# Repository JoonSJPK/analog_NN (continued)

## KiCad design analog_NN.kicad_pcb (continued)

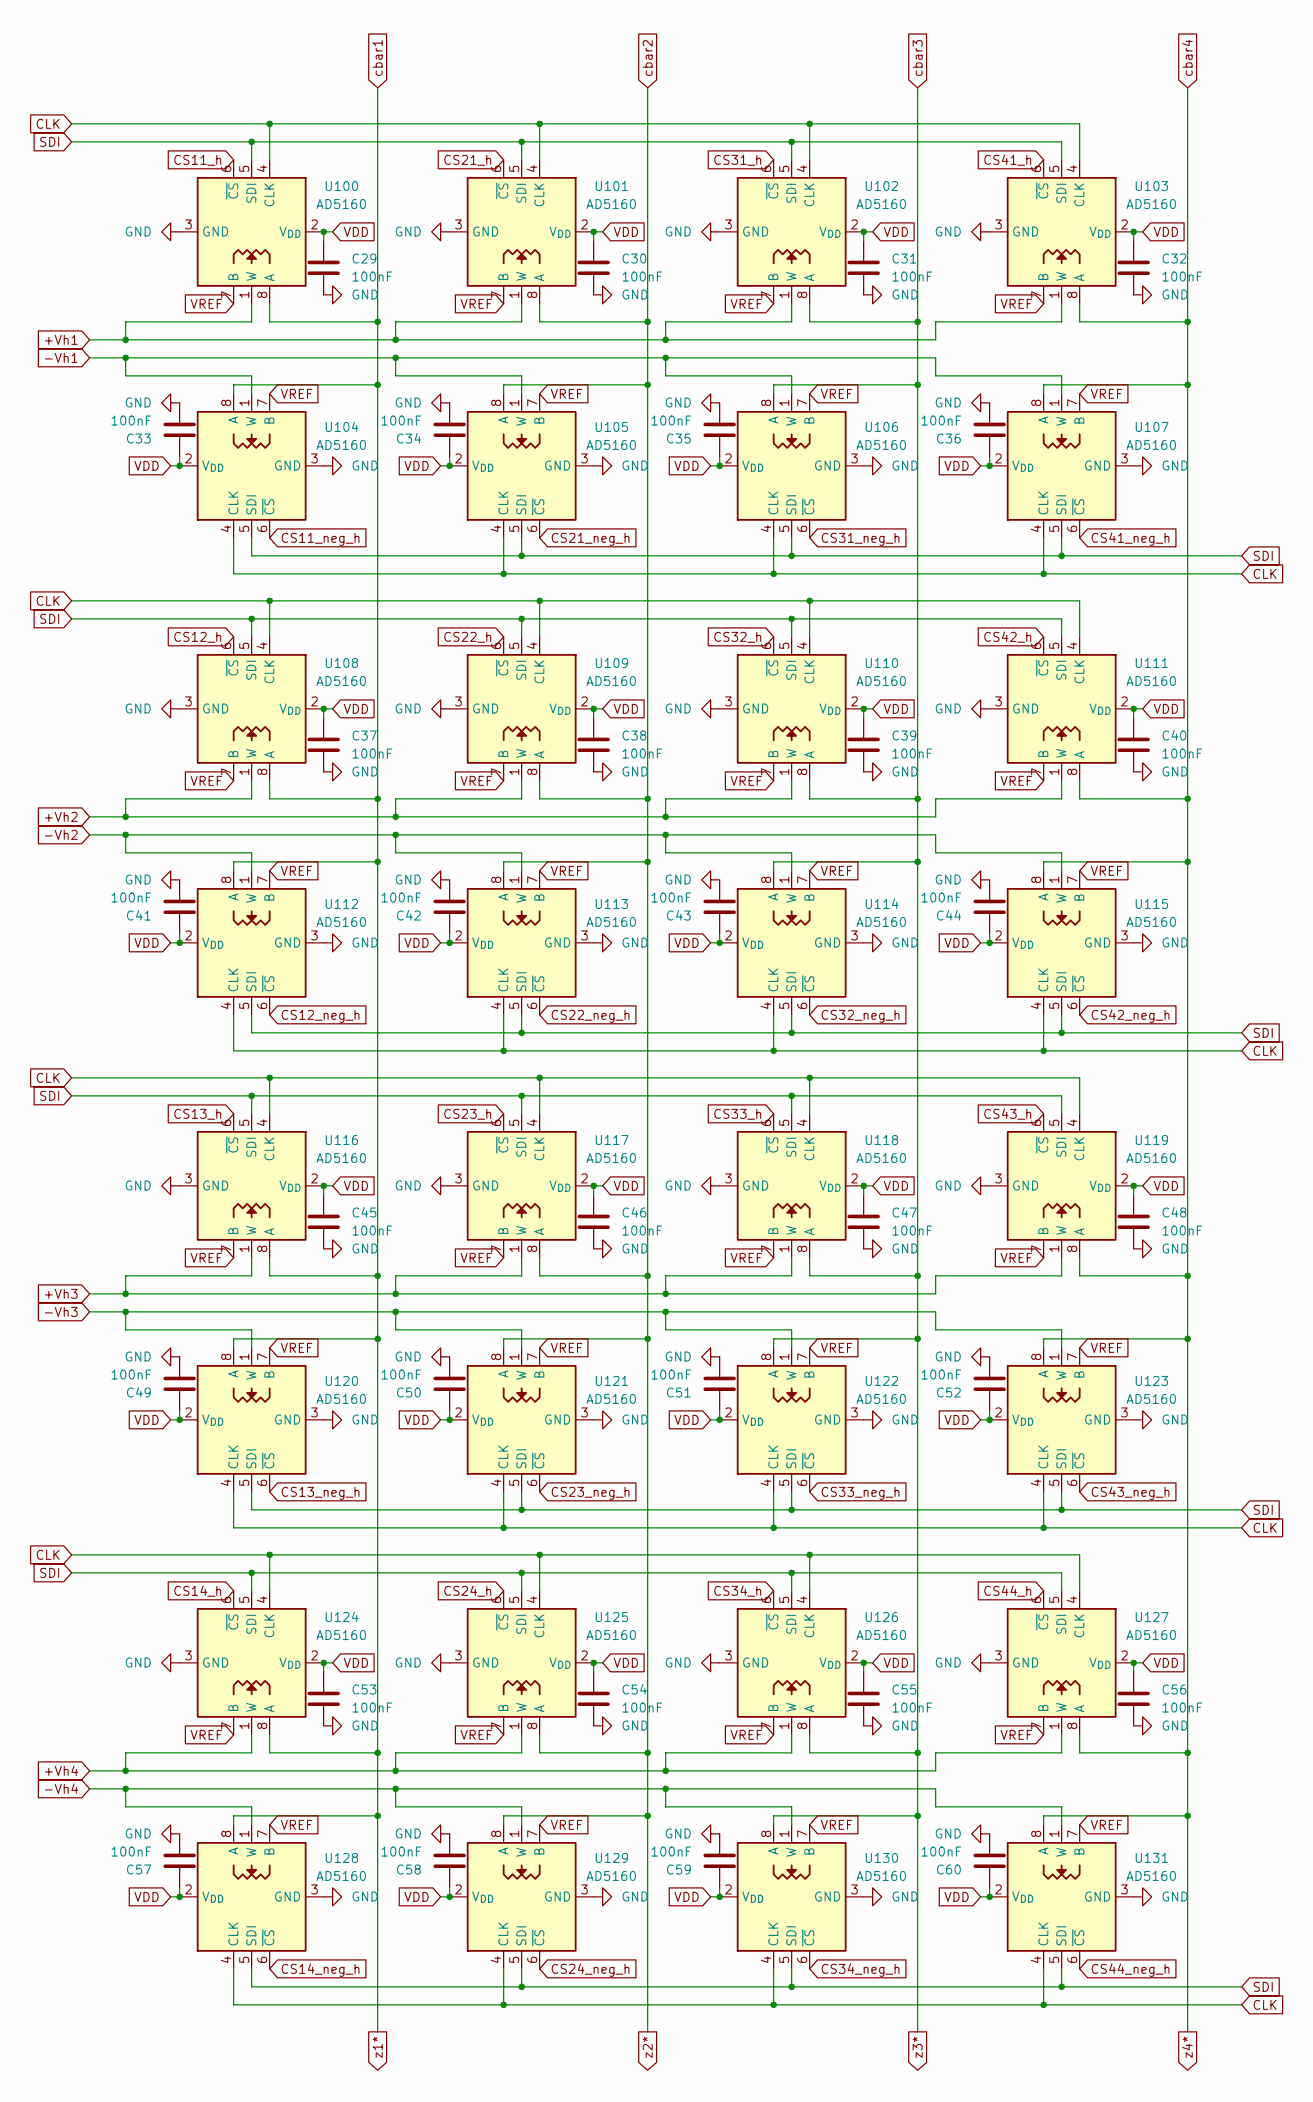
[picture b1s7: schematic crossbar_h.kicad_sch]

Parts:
C29, C30, C31, C32, C33, C34, C35, C36, C37, C38, C39, C40, C41, C42, C43, C44, C45, C46, C47, C48, C49, C50, C51, C52, C53, C54, C55, C56, C57, C58, C59, C60: 100nF; C_1206_3216Metric
U100, U101, U102, U103, U104, U105, U106, U107, U108, U109, U110, U111, U112, U113, U114, U115, U116, U117, U118, U119, U120, U121, U122, U123, U124, U125, U126, U127, U128, U129, U130, U131: AD5160; SOT-23-8

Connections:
+Vh1: U100.1 (W), U101.1 (W), U102.1 (W), U103.1 (W)
+Vh2: U108.1 (W), U109.1 (W), U110.1 (W), U111.1 (W)
+Vh3: U116.1 (W), U117.1 (W), U118.1 (W), U119.1 (W)
+Vh4: U124.1 (W), U125.1 (W), U126.1 (W), U127.1 (W)
-Vh1: U104.1 (W), U105.1 (W), U106.1 (W), U107.1 (W); also elsewhere on the board
-Vh2: U112.1 (W), U113.1 (W), U114.1 (W), U115.1 (W); also elsewhere on the board
-Vh3: U120.1 (W), U121.1 (W), U122.1 (W), U123.1 (W); also elsewhere on the board
-Vh4: U128.1 (W), U129.1 (W), U130.1 (W), U131.1 (W); also elsewhere on the board
CLK: U100.4 (CLK), U101.4 (CLK), U102.4 (CLK), U103.4 (CLK), U104.4 (CLK), U105.4 (CLK), U106.4 (CLK), U107.4 (CLK), U108.4 (CLK), U109.4 (CLK), U110.4 (CLK), U111.4 (CLK), U112.4 (CLK), U113.4 (CLK), U114.4 (CLK), U115.4 (CLK), U116.4 (CLK), U117.4 (CLK), U118.4 (CLK), U119.4 (CLK), U120.4 (CLK), U121.4 (CLK), U122.4 (CLK), U123.4 (CLK), U124.4 (CLK), U125.4 (CLK), U126.4 (CLK), U127.4 (CLK), U128.4 (CLK), U129.4 (CLK), U130.4 (CLK), U131.4 (CLK); also elsewhere on the board
CS11_h: U100.6 (~CS); also elsewhere on the board
CS11_neg_h: U104.6 (~CS); also elsewhere on the board
CS12_h: U108.6 (~CS); also elsewhere on the board
CS12_neg_h: U112.6 (~CS); also elsewhere on the board
CS13_h: U116.6 (~CS); also elsewhere on the board
CS13_neg_h: U120.6 (~CS); also elsewhere on the board
CS14_h: U124.6 (~CS); also elsewhere on the board
CS14_neg_h: U128.6 (~CS); also elsewhere on the board
CS21_h: U101.6 (~CS); also elsewhere on the board
CS21_neg_h: U105.6 (~CS); also elsewhere on the board
CS22_h: U109.6 (~CS); also elsewhere on the board
CS22_neg_h: U113.6 (~CS); also elsewhere on the board
CS23_h: U117.6 (~CS); also elsewhere on the board
CS23_neg_h: U121.6 (~CS); also elsewhere on the board
CS24_h: U125.6 (~CS); also elsewhere on the board
CS24_neg_h: U129.6 (~CS); also elsewhere on the board
CS31_h: U102.6 (~CS); also elsewhere on the board
CS31_neg_h: U106.6 (~CS); also elsewhere on the board
CS32_h: U110.6 (~CS); also elsewhere on the board
CS32_neg_h: U114.6 (~CS); also elsewhere on the board
CS33_h: U118.6 (~CS); also elsewhere on the board
CS33_neg_h: U122.6 (~CS); also elsewhere on the board
CS34_h: U126.6 (~CS); also elsewhere on the board
CS34_neg_h: U130.6 (~CS); also elsewhere on the board
CS41_h: U103.6 (~CS); also elsewhere on the board
CS41_neg_h: U107.6 (~CS); also elsewhere on the board
CS42_h: U111.6 (~CS); also elsewhere on the board
CS42_neg_h: U115.6 (~CS); also elsewhere on the board
CS43_h: U119.6 (~CS); also elsewhere on the board
CS43_neg_h: U123.6 (~CS); also elsewhere on the board
CS44_h: U127.6 (~CS); also elsewhere on the board
CS44_neg_h: U131.6 (~CS); also elsewhere on the board
GND: C29.2, C30.2, C31.2, C32.2, C33.2, C34.2, C35.2, C36.2, C37.2, C38.2, C39.2, C40.2, C41.2, C42.2, C43.2, C44.2, C45.2, C46.2, C47.2, C48.2, C49.2, C50.2, C51.2, C52.2, C53.2, C54.2, C55.2, C56.2, C57.2, C58.2, C59.2, C60.2, U100.3 (GND), U101.3 (GND), U102.3 (GND), U103.3 (GND), U104.3 (GND), U105.3 (GND), U106.3 (GND), U107.3 (GND), U108.3 (GND), U109.3 (GND), U110.3 (GND), U111.3 (GND), U112.3 (GND), U113.3 (GND), U114.3 (GND), U115.3 (GND), U116.3 (GND), U117.3 (GND), U118.3 (GND), U119.3 (GND), U120.3 (GND), U121.3 (GND), U122.3 (GND), U123.3 (GND), U124.3 (GND), U125.3 (GND), U126.3 (GND), U127.3 (GND), U128.3 (GND), U129.3 (GND), U130.3 (GND), U131.3 (GND); also elsewhere on the board
SDI: U100.5 (SDI), U101.5 (SDI), U102.5 (SDI), U103.5 (SDI), U104.5 (SDI), U105.5 (SDI), U106.5 (SDI), U107.5 (SDI), U108.5 (SDI), U109.5 (SDI), U110.5 (SDI), U111.5 (SDI), U112.5 (SDI), U113.5 (SDI), U114.5 (SDI), U115.5 (SDI), U116.5 (SDI), U117.5 (SDI), U118.5 (SDI), U119.5 (SDI), U120.5 (SDI), U121.5 (SDI), U122.5 (SDI), U123.5 (SDI), U124.5 (SDI), U125.5 (SDI), U126.5 (SDI), U127.5 (SDI), U128.5 (SDI), U129.5 (SDI), U130.5 (SDI), U131.5 (SDI); also elsewhere on the board
VDD: C29.1, C30.1, C31.1, C32.1, C33.1, C34.1, C35.1, C36.1, C37.1, C38.1, C39.1, C40.1, C41.1, C42.1, C43.1, C44.1, C45.1, C46.1, C47.1, C48.1, C49.1, C50.1, C51.1, C52.1, C53.1, C54.1, C55.1, C56.1, C57.1, C58.1, C59.1, C60.1, U100.2 (V_{DD}), U101.2 (V_{DD}), U102.2 (V_{DD}), U103.2 (V_{DD}), U104.2 (V_{DD}), U105.2 (V_{DD}), U106.2 (V_{DD}), U107.2 (V_{DD}), U108.2 (V_{DD}), U109.2 (V_{DD}), U110.2 (V_{DD}), U111.2 (V_{DD}), U112.2 (V_{DD}), U113.2 (V_{DD}), U114.2 (V_{DD}), U115.2 (V_{DD}), U116.2 (V_{DD}), U117.2 (V_{DD}), U118.2 (V_{DD}), U119.2 (V_{DD}), U120.2 (V_{DD}), U121.2 (V_{DD}), U122.2 (V_{DD}), U123.2 (V_{DD}), U124.2 (V_{DD}), U125.2 (V_{DD}), U126.2 (V_{DD}), U127.2 (V_{DD}), U128.2 (V_{DD}), U129.2 (V_{DD}), U130.2 (V_{DD}), U131.2 (V_{DD}); also elsewhere on the board
VREF: U100.7 (B), U101.7 (B), U102.7 (B), U103.7 (B), U104.7 (B), U105.7 (B), U106.7 (B), U107.7 (B), U108.7 (B), U109.7 (B), U110.7 (B), U111.7 (B), U112.7 (B), U113.7 (B), U114.7 (B), U115.7 (B), U116.7 (B), U117.7 (B), U118.7 (B), U119.7 (B), U120.7 (B), U121.7 (B), U122.7 (B), U123.7 (B), U124.7 (B), U125.7 (B), U126.7 (B), U127.7 (B), U128.7 (B), U129.7 (B), U130.7 (B), U131.7 (B); also elsewhere on the board
cbar1: U100.8 (A), U104.8 (A), U108.8 (A), U112.8 (A), U116.8 (A), U120.8 (A), U124.8 (A), U128.8 (A); also elsewhere on the board
cbar2: U101.8 (A), U105.8 (A), U109.8 (A), U113.8 (A), U117.8 (A), U121.8 (A), U125.8 (A), U129.8 (A); also elsewhere on the board
cbar3: U102.8 (A), U106.8 (A), U110.8 (A), U114.8 (A), U118.8 (A), U122.8 (A), U126.8 (A), U130.8 (A); also elsewhere on the board
cbar4: U103.8 (A), U107.8 (A), U111.8 (A), U115.8 (A), U119.8 (A), U123.8 (A), U127.8 (A), U131.8 (A); also elsewhere on the board

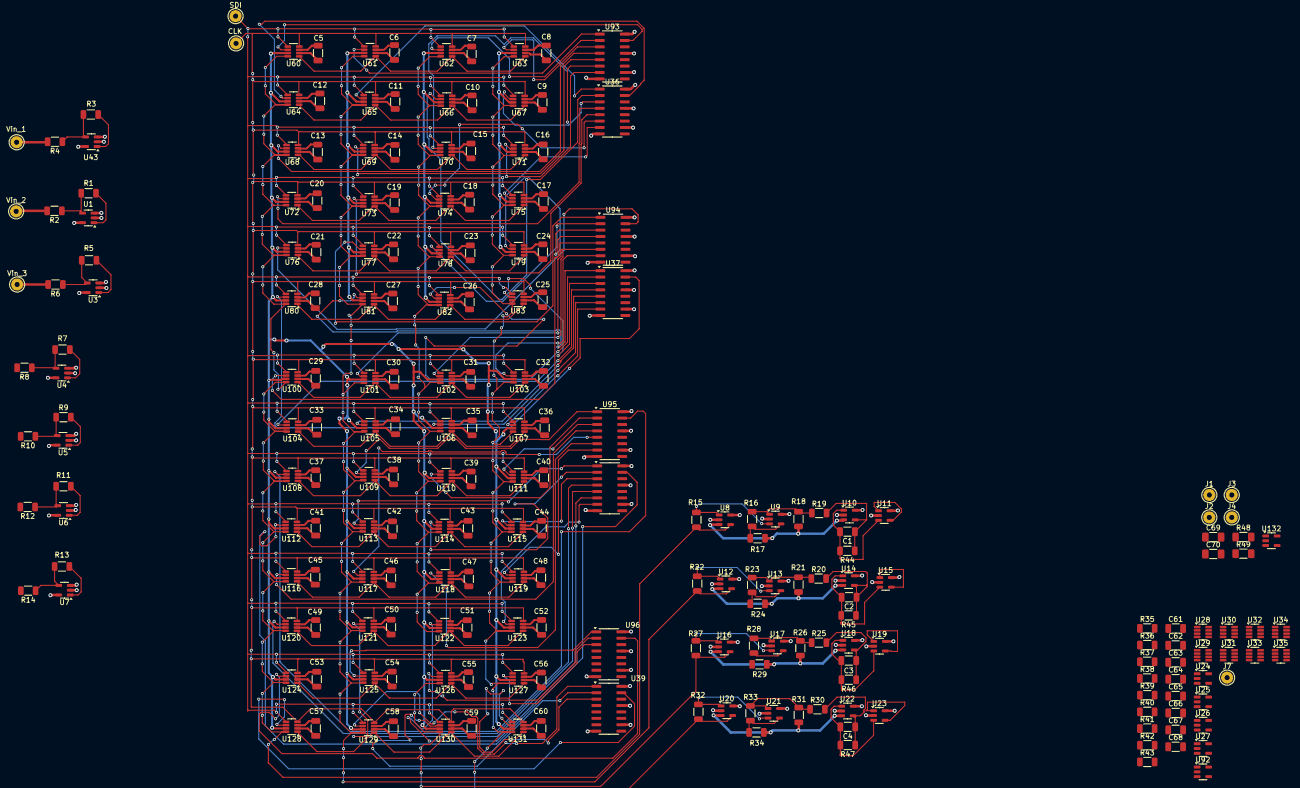
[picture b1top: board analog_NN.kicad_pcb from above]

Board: 4 copper layers, 230 parts (0 on the bottom side), 146 nets.

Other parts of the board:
CLK: Conn_01x01; WireSolderPad_1.0mm
SDI: Conn_01x01; WireSolderPad_1.0mm
Vin_1, Vin_2, Vin_3: Conn_01x01; WireSolderPad_1.0mm

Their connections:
CLK: CLK.1; also elsewhere on the board
SDI: SDI.1; also elsewhere on the board
Vu1: Vin_1.1; also elsewhere on the board
Vu2: Vin_2.1; also elsewhere on the board
Vu3: Vin_3.1; also elsewhere on the board

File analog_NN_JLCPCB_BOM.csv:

Comment,Designator,Footprint,JLC_Class,LCSC_Candidate_VERIFY,Notes
100nF 50V X7R,"C1,C2,C3,C4,C5,C6,C7,C8,C9,C10,C11,C12,C13,C14,C15,C16,C17,C18,C19,C20,C21,C22,C23,C24,C25,C26,C27,C28,C29,C30,C31,C32,C33,C34,C35,C36,C37,C38,C39,C40,C41,C42,C43,C44,C45,C46,C47,C48,C49,C50,C51,C52,C53,C54,C55,C56,C57,C58,C59,C60,C61,C62,C63,C64,C65,C66,C67,C68,C70",C1206,Basic,C29823,Verify: 1206 100nF X7R Basic part
1uF 25V X7R,C69,C1206,Basic,C15849,Verify 1206 1uF X7R
10k 1%,"R1,R2,R3,R4,R5,R6,R7,R8,R9,R10,R11,R12,R13,R14,R15,R16,R17,R18,R19,R20,R21,R22,R23,R24,R25,R26,R27,R28,R29,R30,R31,R32,R33,R34,R35,R36,R37,R38,R39,R40,R41,R42,R43,R48,R49",R1206,Basic,C17888,Verify 1206 10k 1%
10M 1%,"R44,R45,R46,R47",R1206,Basic,C112094,Verify 1206 10M 1%
TLV9061IDBVR,"U1,U3,U4,U5,U6,U7,U8,U9,U10,U11,U12,U13,U14,U15,U16,U17,U18,U19,U20,U21,U22,U23,U24,U25,U26,U27,U43,U132",SOT-23-5,Extended,C398358,"VERIFIED in stock. 29 pcs. NOTE: 27 have blank value in sch (U1-U27) - set to TLV9061IDBVR"
AD5160BRJZ10-RL7,"U28,U29,U30,U31,U32,U33,U34,U35,U60,U61,U62,U63,U64,U65,U66,U67,U68,U69,U70,U71,U72,U73,U74,U75,U76,U77,U78,U79,U80,U81,U82,U83,U100,U101,U102,U103,U104,U105,U106,U107,U108,U109,U110,U111,U112,U113,U114,U115,U116,U117,U118,U119,U120,U121,U122,U123,U124,U125,U126,U127,U128,U129,U130,U131",SOT-23-8,Extended,C40097,"VERIFIED ~5295 in stock (~$1.37). 10k variant. 100k variant = C578141. 64 pcs/board"
SN74HC595DR,"U36,U37,U38,U39,U93,U94,U95,U96",SOIC-16,Basic,C5947,"VERIFIED Basic (Nexperia 74HC595D). TI SN74HC595DR = C10092"
